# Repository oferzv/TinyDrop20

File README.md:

# TinyDrop20

TinyDrop20 is a small ATtiny85-based 5x4 charlieplexed LED matrix board. The
repository contains the PlatformIO firmware project, Eagle design files, and
manufacturing outputs for hardware revision `V1_1`.

## Project background

This project was created in collaboration with [@talofer99](https://github.com/talofer99)
as part of a series of free-time hardware and firmware projects we built years
ago. I decided to move these projects to GitHub in the hope that they may be
useful, educational, or inspiring to others.

This PCB revision was manufactured and tested.

## Repository layout

```text
Firmware/
  V1_1/
    platformio.ini      PlatformIO project configuration
    src/main.cpp        ATtiny85 firmware
    include/            Project headers, currently unused
    lib/                Project libraries, currently unused
    test/               PlatformIO test folder, currently unused

Hardware/
  V1_1/
    Eagle/              Eagle schematic and board files
    Manufacturing/
      GERBER/           Gerber package for PCB fabrication
      Schematic/        Exported schematic PDF
```

## Hardware overview

The V1.1 board is built around an `ATTINY85-20SU` microcontroller and a 20 LED
display arranged as a 5 row by 4 column matrix. The LEDs are 0603 green parts
driven through five 100 ohm resistors from ATtiny pins `PB0` through `PB4`.

Other notable hardware:

- 20 green 0603 matrix LEDs
- 1 red 0603 status LED
- ATtiny85 SOIC-8 microcontroller
- Five 100 ohm matrix resistors
- 10 kOhm reset pull-up resistor
- Micro USB connector
- MCP73831 battery charger circuit
- CR2450-size coin-cell holder footprint
- Six round test points for programming or probing
- 3.6 mm mounting pad

Power note: the schematic includes an MCP73831 Li-ion/LiPo charger and a battery
holder labeled `CR2450`. Standard CR2450 cells are not rechargeable. Before
connecting USB power with a cell installed, verify that the assembled board is
intended for a compatible rechargeable lithium coin cell, such as the exact cell
specified by the hardware build.

## Firmware overview

The firmware is an Arduino sketch built with PlatformIO for `attiny85` at
8 MHz. It drives the LEDs directly by changing ATtiny GPIO direction and output
state for charlieplexing.

Display constants in `Firmware/V1_1/src/main.cpp`:

```cpp
#define SPEED          35
#define DISPLAY_WIDTH  4
#define DISPLAY_HEIGHT 5
```

The sketch includes:

- A 4x5 bitmap font for uppercase letters, digits, space, `!`, `#`, `$`, and
  `^`
- `setLed()` and `setPixel()` helpers for charlieplexed LED control
- `renderCharacter()` and `renderString()` helpers for drawing text
- Several visual modes and effects:
  - `matrix_fill_test()`
  - `write_text()`
  - `scrolling_text()`
  - `screen_saver()`
  - `rainEffect()`
  - `rows_effect()`

The current sketch displays `myString`, defined near the top of `main.cpp`:

```cpp
char myString[] = "#$^";
```

In the checked-in firmware, `lastState` is hardcoded to `1`, so `setup()` sets
`mode = 0` and the main loop runs `matrix_fill_test()`. The EEPROM-based mode
toggle code is present but commented out.

## Build firmware

Install PlatformIO, then build from the firmware directory:

```powershell
cd Firmware\V1_1
pio run
```

Build output is generated under:

```text
Firmware/V1_1/.pio/build/attiny85/
```

The main outputs are `firmware.elf` and `firmware.hex`.

## Upload firmware

The PlatformIO environment is configured for a USBtiny-compatible ISP
programmer:

```ini
[env:attiny85]
platform = atmelavr
board = attiny85
framework = arduino
board_build.mcu = attiny85
board_build.f_cpu = 8000000L
upload_protocol = usbtiny
```

Connect the programmer to the ATtiny85 programming pads or test points, then
run:

```powershell
cd Firmware\V1_1
pio run -t upload
```

The Micro USB connector on the hardware is part of the board power and charger
circuit. The firmware configuration expects ISP programming with `usbtiny`, not
USB bootloader programming.

## Hardware files

Open the board in Autodesk Eagle/Fusion Electronics using:

```text
Hardware/V1_1/Eagle/TinyDrop20_V1_1.sch
Hardware/V1_1/Eagle/TinyDrop20_V1_1.brd
```

Manufacturing files are already exported:

```text
Hardware/V1_1/Manufacturing/GERBER/TinyDrop20_V1_1_2020_03_09.zip
Hardware/V1_1/Manufacturing/Schematic/TinyDrop20_V1_1.pdf
```

## Development notes

- The charlieplexing code uses ATtiny pins `0` through `4`, corresponding to
  `PB0` through `PB4` in the schematic.
- Only one LED is actively driven at a time. Persistent images are produced by
  repeatedly scanning pixels fast enough for persistence of vision.
- To show different text, update `myString` in `src/main.cpp`.
- To enable the text display mode, set `mode = 1` or re-enable the EEPROM mode
  selection logic.
- Generated PlatformIO build files under `.pio/` should not be committed.

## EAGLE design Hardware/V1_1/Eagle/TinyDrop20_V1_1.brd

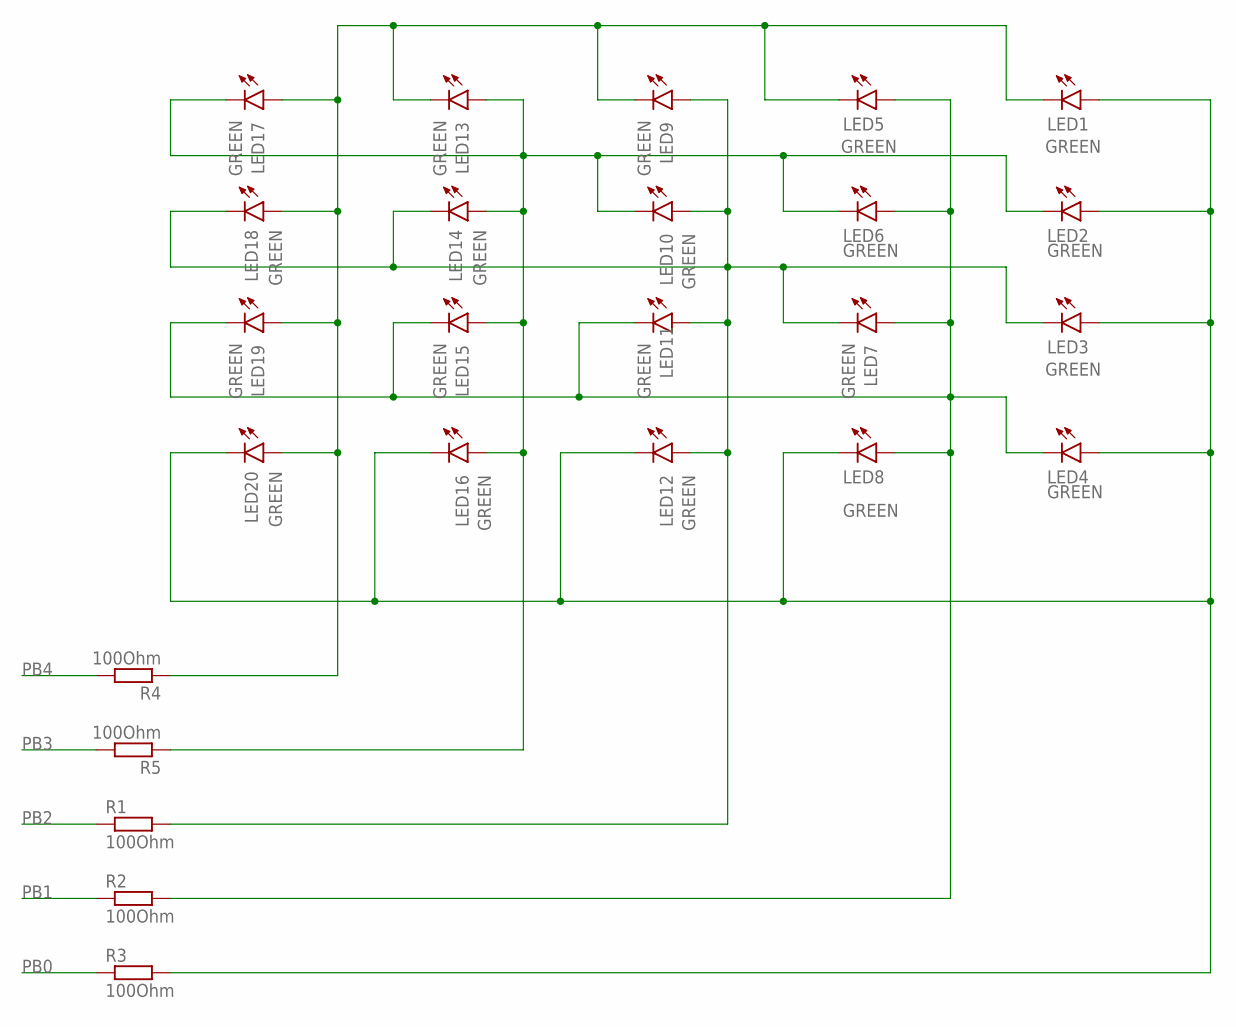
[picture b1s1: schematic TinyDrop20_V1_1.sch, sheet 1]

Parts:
LED1, LED2, LED3, LED4, LED5, LED6, LED7, LED8, LED9, LED10, LED11, LED12, LED13, LED14, LED15, LED16, LED17, LED18, LED19, LED20: GREEN; CHIPLED_0603
R1, R2, R3, R4, R5: 100Ohm; R0603

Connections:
unnamed: LED1.A, LED2.A, LED3.A, LED4.A, LED8.C, LED12.C, LED16.C, LED20.C, R3.2
unnamed: LED4.C, LED5.A, LED6.A, LED7.A, LED8.A, LED11.C, LED15.C, LED19.C, R2.2
unnamed: LED3.C, LED7.C, LED9.A, LED10.A, LED11.A, LED12.A, LED14.C, LED18.C, R1.2
unnamed: LED2.C, LED6.C, LED10.C, LED13.A, LED14.A, LED15.A, LED16.A, LED17.C, R5.1
unnamed: LED1.C, LED5.C, LED9.C, LED13.C, LED17.A, LED18.A, LED19.A, LED20.A, R4.1
PB0: R3.1; also elsewhere on the board
PB1: R2.1; also elsewhere on the board
PB2: R1.1; also elsewhere on the board
PB3: R5.2; also elsewhere on the board
PB4: R4.2; also elsewhere on the board

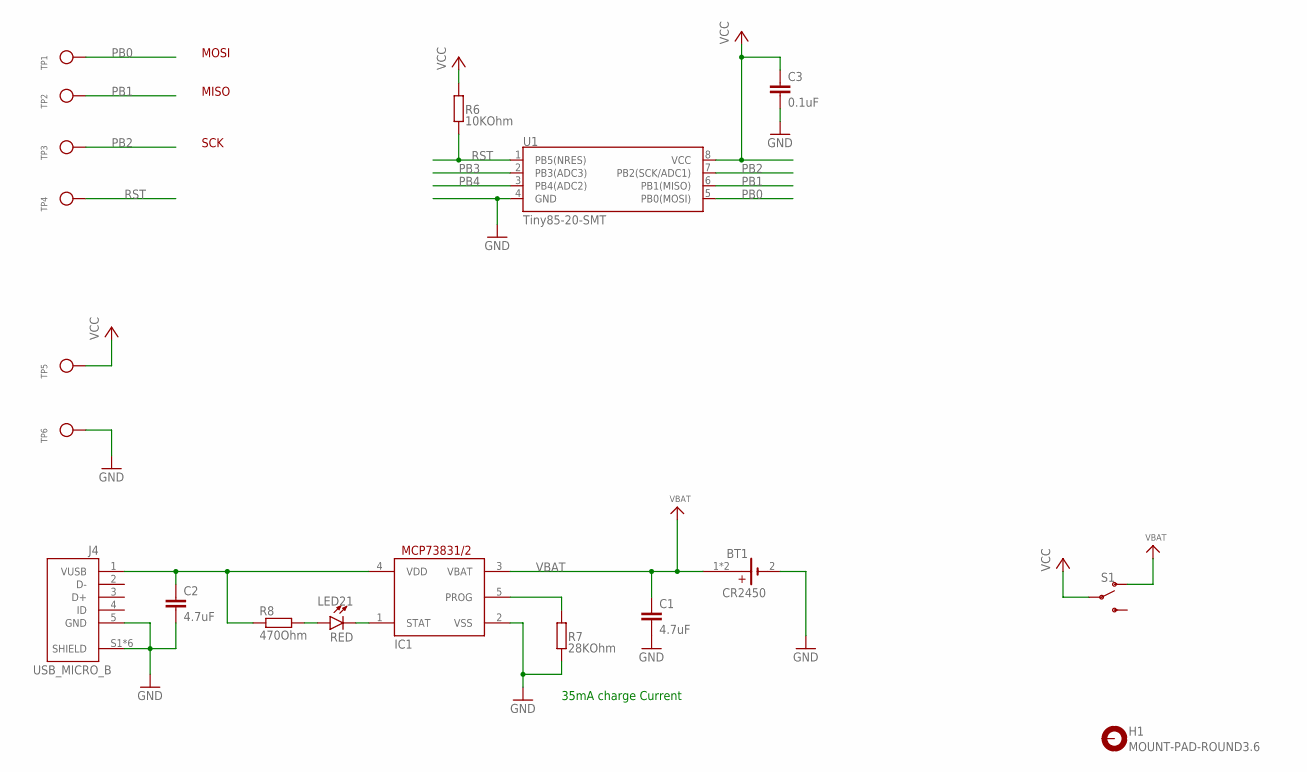
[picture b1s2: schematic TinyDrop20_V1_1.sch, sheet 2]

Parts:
BT1: CR2450; BATTCON_24.5X5MM_SMD
C1, C2: 4.7uF; C0805
C3: 0.1uF; C0805
H1: MOUNT-PAD-ROUND3.6; 3,6-PAD
IC1: MCP73831/OT; SOT23-5L
J4: USB_MICRO_B; FCI_10118193-0001LF
LED21: RED; CHIPLED_0603
R6: 10KOhm; R0603
R7: 28KOhm; R0603
R8: 470Ohm; R0603
S1: SWITCH-SPDT-SMD-RIGHT-ANGLE; SWITCH_SPST_SMD_A
TP1, TP2, TP3, TP4, TP5, TP6: TESTPOINTROUND2MM; TESTPOINT_ROUND_2MM
U1: Tiny85-20-SMT; SO08-EIAJ_MCU

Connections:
GND: BT1.2 (-), C1.2, C2.2, C3.2, IC1.2 (VSS), J4.5 (GND), J4.S1 (SHIELD), J4.S2 (SHIELD), J4.S3 (SHIELD), J4.S4 (SHIELD), J4.S5 (SHIELD), J4.S6 (SHIELD), R7.1, TP6.P$1, U1.4 (GND)
unnamed: IC1.5 (PROG), R7.2
unnamed: C2.1, IC1.4 (VDD), J4.1 (VUSB), R8.1
unnamed: IC1.1 (STAT), LED21.C
unnamed: LED21.A, R8.2
PB0: TP1.P$1, U1.5 (PB0(MOSI)); also elsewhere on the board
PB1: TP2.P$1, U1.6 (PB1(MISO)); also elsewhere on the board
PB2: TP3.P$1, U1.7 (PB2(SCK/ADC1)); also elsewhere on the board
PB3: U1.2 (PB3(ADC3)); also elsewhere on the board
PB4: U1.3 (PB4(ADC2)); also elsewhere on the board
RST: R6.1, TP4.P$1, U1.1 (PB5(NRES))
VBAT: BT1.1 (+), BT1.3 (+), C1.1, IC1.3 (VBAT), S1.1 (O)
VCC: C3.1, R6.2, S1.2, TP5.P$1, U1.8 (VCC)

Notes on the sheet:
35mA charge Current
MOSI
MISO
SCK

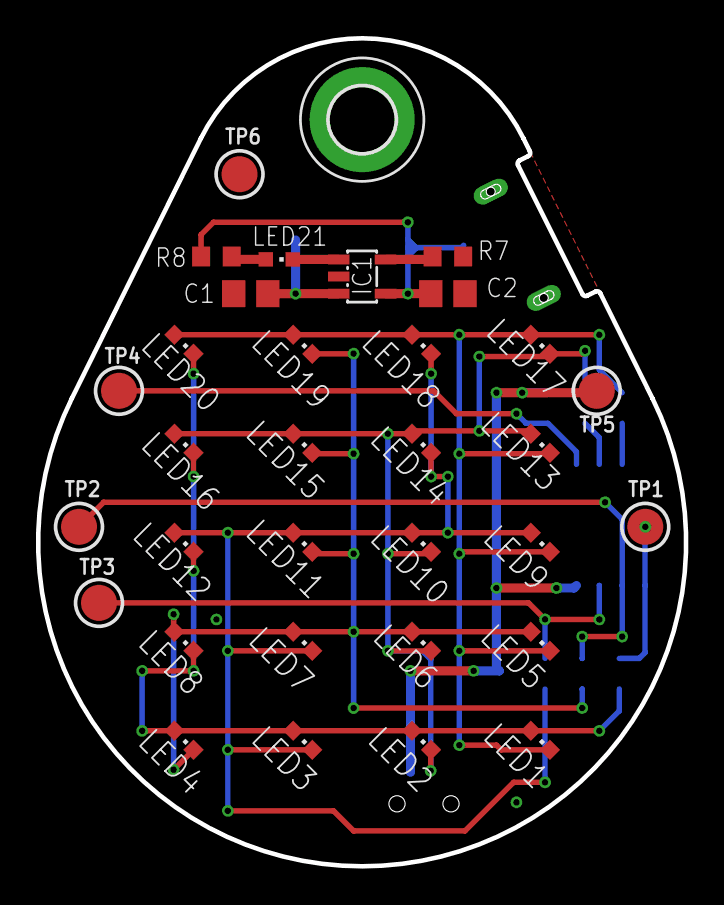
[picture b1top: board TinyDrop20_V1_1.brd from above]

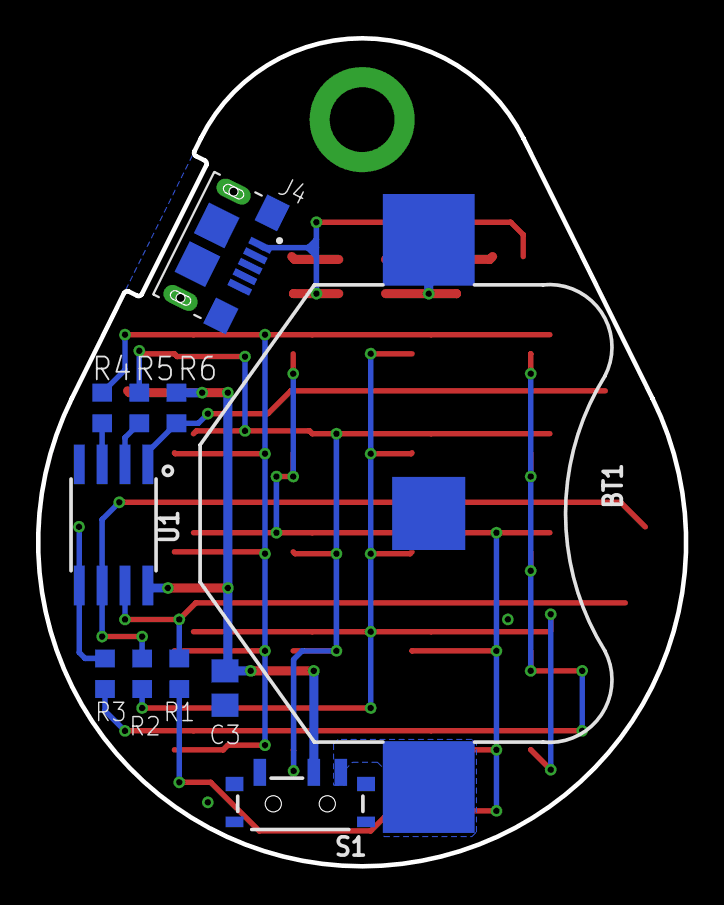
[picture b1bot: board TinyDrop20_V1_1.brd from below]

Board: 2 copper layers, 36.0 x 46.0 mm, 44 parts (11 on the bottom side), 18 nets.

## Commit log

2026-06-04 Eagle project files of the manufactured version
2026-06-04 Adding Schematic PDF file
2026-06-04 Add initial project files including .gitignore, platformio.ini, and source code
2026-06-04 Update README.md with detailed project description, repository layout, hardware and firmware overviews, build and upload instructions, and development notes.
2026-06-09 Add project background to README
2026-06-13 Add PCB manufacturing note

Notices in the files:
parts and their libraries:
SparkFun-Switches: Licensing: Creative Commons ShareAlike 4.0 International - https://creativecommons.org/licenses/by-sa/4.0
microbuilder: This work is placed in the public domain, and may be freely used for commercial and non-commercial work with the following conditions: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
